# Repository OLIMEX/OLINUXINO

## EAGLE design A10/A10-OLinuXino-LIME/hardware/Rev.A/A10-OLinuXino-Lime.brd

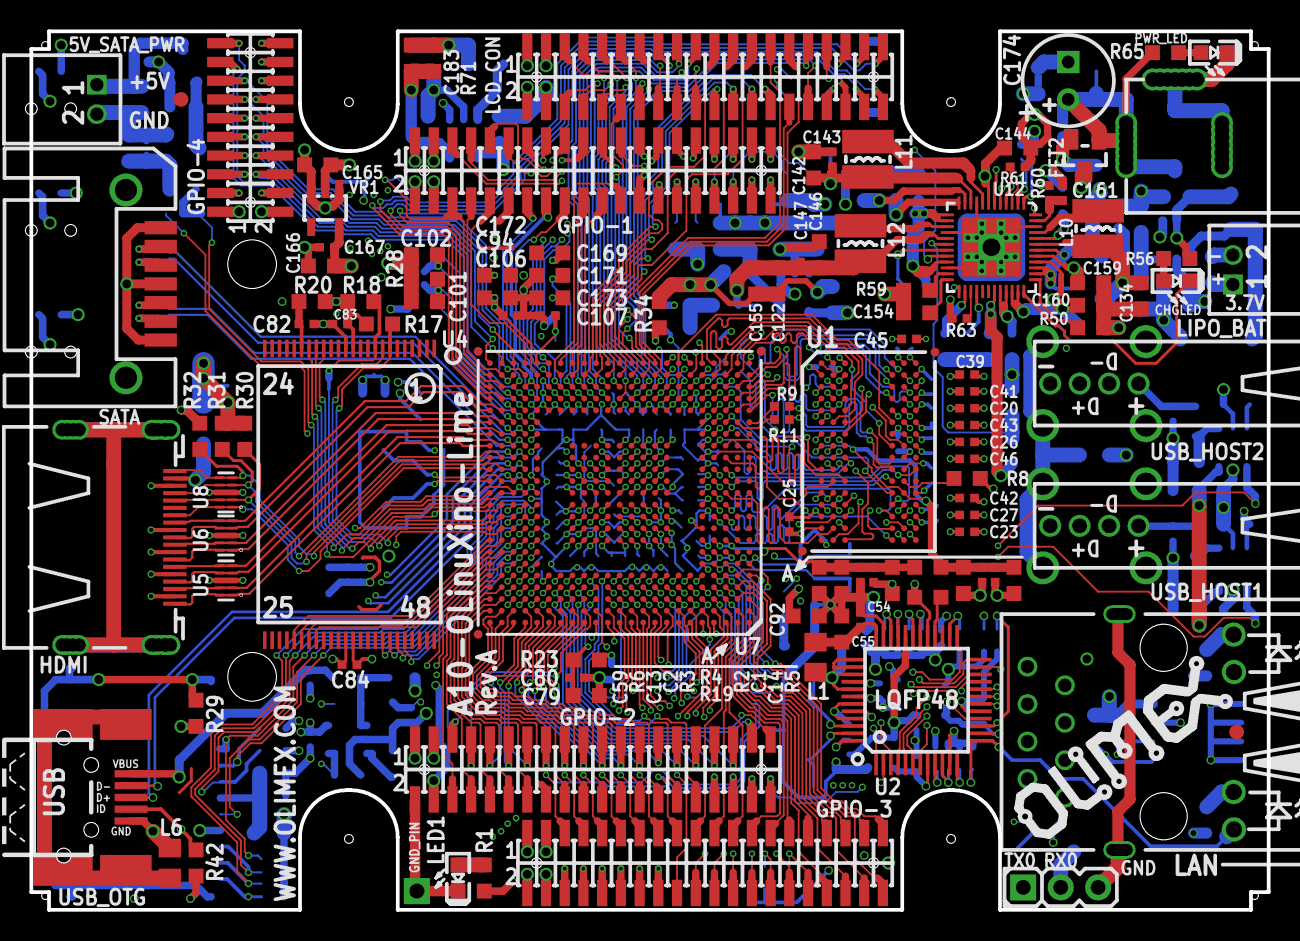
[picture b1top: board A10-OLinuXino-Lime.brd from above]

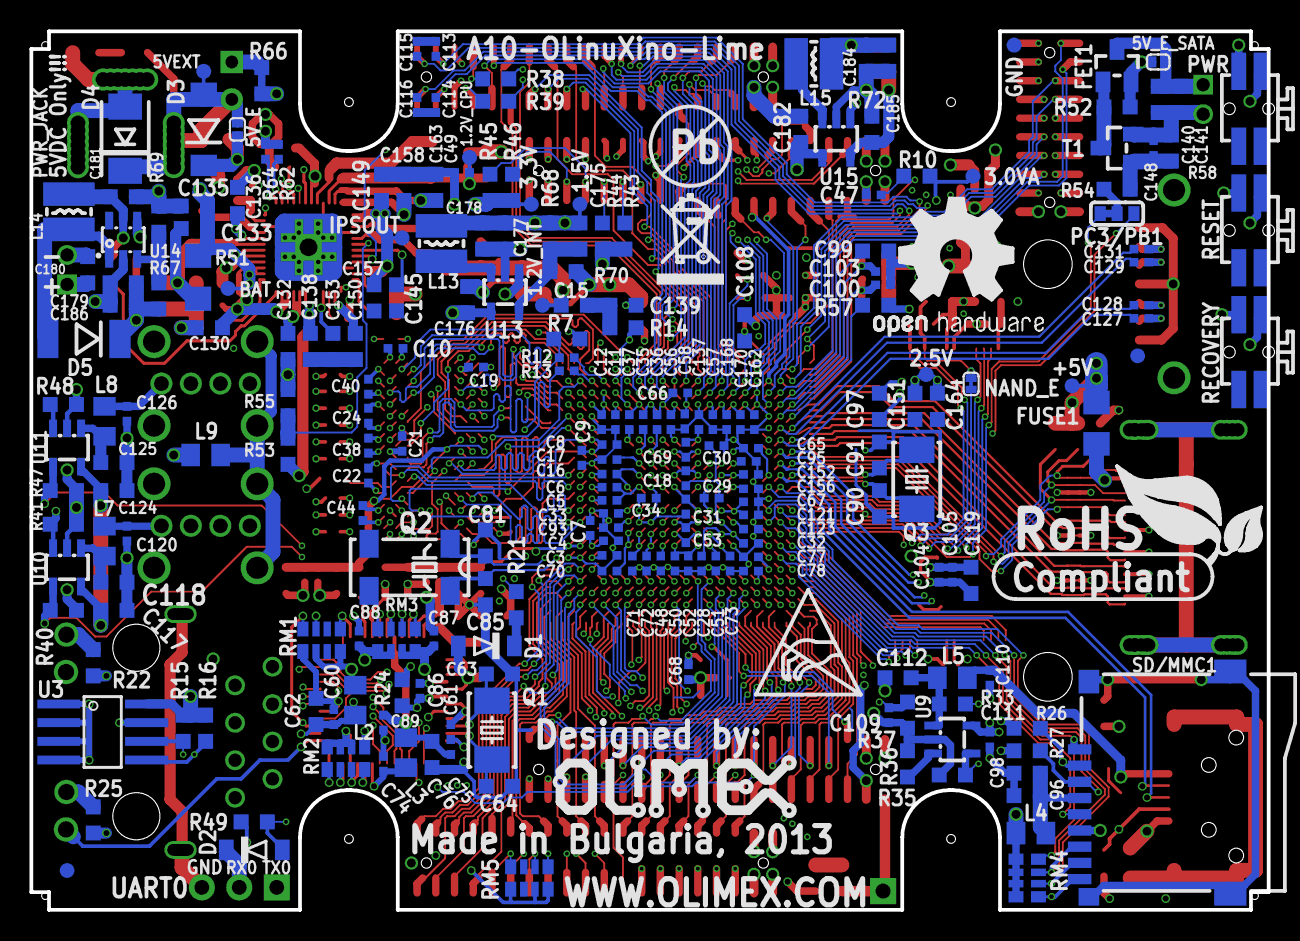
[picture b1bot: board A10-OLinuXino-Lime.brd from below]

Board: 6 copper layers, 84.0 x 59.6 mm, 356 parts (239 on the bottom side), 388 nets.

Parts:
1.2V_CPU, 1.2V_INT, 1.5V, 2.5V, 3.0VA, 3.3V, 5VEXT: TESTPADTESTPAD_40-ROUND; TESTPAD_40-ROUND
5V_E: Open; SJ_1_SMALLER
5V_E_SATA: SJ_1_SMALLER
5V_SATA_PWR: CON2DW02R; DW02R
+5V: TESTPADTESTPAD_40-ROUND; TESTPAD_40-ROUND
BAT: TESTPADTESTPAD_40-ROUND; TESTPAD_40-ROUND
C1, C2, C3, C4, C5, C6, C7, C8, C9, C10, C11, C12, C13, C14, C16, C17, C18, C19, C20, C21, C22, C23, C24, C25, C26, C27, C28, C29, C30, C31, C32, C33, C34, C35, C36, C37, C38, C39, C40, C41, C42, C43, C44, C45, C46, C48, C49, C50, C51, C52, C53, C56, C57, C58, C65, C66, C67, C68, C69, C70, C71, C72, C73, C77, C78, C95, C100, C103, C104, C105, C106, C107, C121, C123, C137, C152, C156, C162, C168, C170: 220nF; C0402_TI
C15, C55, C62, C76, C92, C94, C96, C97, C98, C112, C118, C119, C122, C125, C139, C140, C151, C155, C164, C165, C166, C169, C172, C176, C177, C178, C179, C180, C181, C182, C184, C185, C186: 22uF/6.3V; C0603_DWS
C47, C113, C114, C115, C116, C143, C147, C161: 1nF; C0402_TI
C54, C60, C61, C74, C75, C80, C82, C83, C84, C86, C87, C88, C89, C93, C109, C110, C111, C120, C126, C148, C167: 100nF; C0402_TI
C59: NA; C0603_DWS
C63, C64, C90, C91: 33pF; C0603_DWS
C79, C99, C133, C145, C150, C154: 1uF; C0603_DWS
C81, C85: 10pF; C0603_DWS
C101, C102, C108, C117, C124, C130, C132, C134, C135, C136, C138, C142, C144, C146, C149, C153, C157, C158, C159, C160, C163: 10uF/6.3V; C0603_DWS
C127, C128, C129, C131: 10nF; C0402_TI
C141: NA(22uF/6.3V); C0603_DWS
C171, C173: 470nF; C0603_DWS
C174: 470uF/10V/105C; E2,5-6,3
C175, C183: 22pF; C0603_DWS
CHGLED: LED/YELLOW/0603; LED-0603
D1, D2: 1N5819(S4SOD-123); SOD-123
D3: 1N5822/SS34/SMA; MLL-41
D4: SMBJ6.0A; DO214AA
D5: 1N5822/SS34/SMA; MELF-MLL41
FET1, FET2: IRLML6402; SOT23
FUSE1: FSMD035; 1206
GND: TESTPADTESTPAD_40-ROUND; TESTPAD_40-ROUND
GND_PIN: TESTPAD3; TEST_PAD40/70/SQUARE
GPIO-1, GPIO-2, GPIO-3: ML40YA-V36P-2X20-LF; YA-V36P-2X20-LF
GPIO-4: ML20YA-V36P-2X10-LF; YA-V36P-2X10-LF
HDMI: HDMI-SWM-19
IPSOUT: TESTPADTESTPAD_40-ROUND; TESTPAD_40-ROUND
L1, L2, L3, L5, L6, L7, L8, L9: FB0805/600R/2A; L0805_5MIL_DWS
L4: CL470nH/0805/1.76R/250mA; L0805_5MIL_DWS
L10, L11, L12, L13, L14, L15: 2.2uH/1.5A/DCR<0.1R/CD32; CD32
LAN: RJLBC-060TC1_GND_MILLING; RJLBC-060TC1_MILLING
LCD_CON: ML40YA-V36P-2X20-LF; YA-V36P-2X20-LF
LED1: LED/GREEN/0603; LED-0603
LIPO_BAT: CON2DW02R; DW02R
NAND_E: Close; SJ_1_SMALLER_CLOSE_10MILS
PC3/PB1: SJ_2_SMALL_23_TIED
PWR: SIDE_WTCM-TR(3X4); SW_TAKT3X4
PWR_JACK: YDJ-1136; PWR_JACK_UNI_MILLING
PWR_LED: LED/RED/0603; LED-0603
Q1: 4SB25.000F20E15/5x3.2mm/20ppm/20pF; HCX-4S
Q2: 32768Hz/6pF; MC-306
Q3: 4SB24.000F20E15/5x3.2mm/20ppm/20pF; HCX-4S
R1, R43, R44, R45, R46, R56, R65: 2.2k; R0603_5MIL_DWS
R2, R3, R5, R6, R7, R19, R30, R31: 2k/1%; R0603_5MIL_DWS
R4, R24, R38, R39: NA; R0603_5MIL_DWS
R8: 237R/1%; R0603_5MIL_DWS
R9, R11: 22R; R0402_TI
R10, R26, R53: 100k/1%; R0603_5MIL_DWS
R12, R13: NA(Close_0R); R0402_TI
R14: 330R/1%; R0603_5MIL_DWS
R15, R16: NA(2.2k); R0603_5MIL_DWS
R17, R18, R20, R27, R29, R35, R37, R40, R47, R49, R52, R54: 10k; R0603_5MIL_DWS
R21, R23, R32, R42: 47k; R0603_5MIL_DWS
R22, R25: 560R; R0603_5MIL_DWS
R28, R55, R59: 200k/1%; R0603_5MIL_DWS
R33, R58, R68, R71: 4.99k/1%; R0603_5MIL_DWS
R34: NA(0R); R0603_5MIL_DWS
R36, R41, R48: 13k/1%; R0603_5MIL_DWS
R50: 100R; R0603_5MIL_DWS
R51: 0.03R/1%; R1206_5MIL_WS
R57: 191R/1%; R0603_5MIL_DWS
R60, R61, R62, R63, R64: 2.2k; R0402_TI
R66: 0R(Board_Mounted); 0603_0R
R67: 8.25k/1%; R0603_5MIL_DWS
R69, R72: 1.1k/1%; R0603_5MIL_DWS
R70: 3.32k/1%; R0603_5MIL_DWS
RECOVERY: SIDE_WTCM-TR(3X4); SW_TAKT3X4
RESET: SIDE_WTCM-TR(3X4); SW_TAKT3X4
RM1, RM2: RA1206_(4X0603)_4B8_4.7k; R_MATRIX_4
RM3: RA1206_(4X0603)_4B8_51R; R_MATRIX_4
RM4: RA1206_(4X0603)_4B8_100K; R_MATRIX_4
RM5: RA1206_(4X0603)_4B8_10k; R_MATRIX_4
SATA: SATA-PWA-07
SD/MMC1: MICRO_SD/MMC_CP_NEWTFC-WPAPR-08; TFC-WPAPR-08
T1: BC846B; SOT23
U1: MEM4G16D3EABG-125; FBGA96_MEM
U2: RTL8201CP; LQFP48
U3: AT24C16BN-SH; SO-08MN
U4: H27UBG8T2BTR; TSOP48
U5, U6, U8: NA(RCLAMP0524P); SLP2510P8
U7: A10; TFBGA441
U9, U10, U11: SY6280; SOT23-5
U12: AXP209(QFN48); QFN48
U13, U15: SY8008C(AA)C; SOT23-5
U14: SY7208(SOT23-6); SOT23-6
U16, U17, U18, U19: FIDUCIAL; FIDUCIAL-1X3
U$2: HAMMOND_1593LBK_A10_LIME
U$5: LOGO-OPENHARDWARE_8X8
U$6, U$8: OLIMEX1_V
U$9: PB
U$10: ESD_SYMBOL
U$11: RECYCLE_BIN1/8
U$12: ROHS
UART0: HN1X3
USB_HOST1, USB_HOST2: USB_A_VERTICAL; USB_A_VERTICAL_PTH
USB_OTG: USB-OTG; USB_MINI_9PIN
VR1: AP1231-2.5V(SOT23-5); SOT-23-5

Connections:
5VEXT: 5VEXT.1, 5V_E.1, C132.2, C174.+, D3.A, D4.C, FET2.1, PWR_JACK.+, R65.1, U12.32, U12.33
+5V: 5V_E.2, 5V_E_SATA.1, +5V.1, C111.1, C117.1, C124.1, D3.K, FET1.2, FET2.2, FUSE1.1, GPIO-1.1, GPIO-2.1, GPIO-3.1, LCD_CON.1, R30.2, R31.2, R52.1, U9.5, U10.5, U11.5
+5V_OTG_PWR: C110.1, C138.2, L5.1, R53.1, U12.31, USB_OTG.VBUS
+24V: BAT.1, C133.2, C135.1, C180.2, LIPO_BAT.1, R51.2, U12.38, U12.39, U12.42
BA0: U1.M2, U7.K3
BA1: U1.N8, U7.L4
BA2: U1.M3, U7.K4
CASN: U1.K3, U7.U3
CKE: U1.K9, U7.N3
CLK: R9.1, U1.J7
CLKN: R11.1, U1.K7
CPU-REF: C2.2, C13.2, C59.2, R3.1, R4.2, R6.2, U7.AA8, U7.H3, U7.H4, U7.Y5
DDR3_ODT: R13.1, U1.K1
DDR3_RST: R7.1, R12.1, U1.T2
DDR_VREF: C1.2, C14.2, R2.1, R4.1, R5.2, U1.H1, U1.M8
DQ0: U1.E3, U7.AB4
DQ1: U1.F7, U7.AC7
DQ2: U1.F2, U7.AC4
DQ3: U1.F8, U7.AB8
DQ4: U1.H3, U7.AC8
DQ5: U1.H8, U7.AB5
DQ6: U1.G2, U7.AB7
DQ7: U1.H7, U7.AC3
DQ8: U1.D7, U7.AB2
DQ9: U1.C3, U7.Y1
DQ10: U1.C8, U7.AC2
DQ11: U1.C2, U7.Y2
DQ12: U1.A7, U7.AA1
DQ13: U1.A2, U7.AB3
DQ14: U1.B8, U7.W2
DQ15: U1.A3, U7.AC1
ECOL: U2.1, U7.D13
ECRS: U2.23, U7.E12
EMDC: U2.25, U7.E10
EMDIO: RM1.1.1, U2.26, U7.D11
EPHY-RST#: R24.1, U7.C13
ERXCK: U2.16, U7.D9
ERXD0: U2.21, U7.E6
ERXD1: U2.20, U7.D6
ERXD2: U2.19, U7.E5
ERXD3: U2.18, U7.D5
ERXDV: U2.22, U7.D10
ERXERR: U2.24, U7.E9
ETXCK: U2.7, U7.D12
ETXD0: U2.6, U7.E8
ETXD1: U2.5, U7.D8
ETXD2: U2.4, U7.E7
ETXD3: U2.3, U7.D7
ETXEN: U2.2, U7.E11
EXTEN: U12.20, U14.4, U15.1
FMINL: GPIO-4.19, U7.Y20
FMINR: GPIO-4.17, U7.Y21
GND: 5V_SATA_PWR.2, C3.1, C4.1, C5.1, C6.1, C7.1, C8.1, C9.1, C10.1, C11.1, C12.1, C13.1, C14.1, C15.1, C16.1, C17.1, C18.1, C19.1, C20.1, C21.1, C22.1, C23.1, C24.1, C25.1, C26.1, C27.1, C28.1, C29.1, C30.1, C31.1, C32.1, C33.1, C34.1, C35.1, C36.1, C37.1, C38.1, C39.1, C40.1, C41.1, C42.1, C43.1, C44.1, C45.1, C46.1, C48.1, C49.1, C50.1, C51.1, C52.1, C53.1, C54.1, C55.1, C56.1, C57.1, C58.1, C59.1, C60.1, C61.1, C62.1, C63.1, C64.1, C65.1, C66.1, C67.1, C68.1, C69.1, C70.1, C71.1, C72.1, C73.1, C74.2, C75.2, C76.2, C77.1, C78.1, C79.1, C80.1, C81.1, C82.1, C83.1, C84.1, C85.1, C86.1, C87.1, C88.1, C89.1, C90.1, C91.1, C92.1, C93.1, C94.1, C95.1, C96.1, C98.1, C104.1, C105.1, C106.1, C107.1, C108.1, C109.2, C110.2, C111.2, C112.1, C113.1, C114.1, C115.1, C116.1, C117.2, C118.1, C119.1, C120.2, C121.1, C122.1, C123.1, C124.2, C125.1, C126.2, C130.1, C132.1, C134.2, C135.2, C136.2, C137.2, C138.1, C139.1, C140.1, C141.1, C142.2, C143.2, C144.2, C145.1, C146.2, C147.2, C148.2, C149.2, C150.1, C151.1, C152.1, C153.2, C154.1, C155.1, C156.1, C157.1, C158.2, C159.2, C160.2, C161.1, C162.2, C163.2, C164.1, C165.2, C166.2, C167.2, C168.2, C169.1, C170.2, C171.1, C172.1, C173.1, C174.-, C176.2, C177.2, C178.2, C179.2, C180.1, C181.1, C182.2, C184.2, C185.2, C186.2, D4.A, GND.1, GND_PIN.P$1, GPIO-1.2, GPIO-2.2, GPIO-3.2, GPIO-3.4, GPIO-4.2, HDMI.2, HDMI.5, HDMI.8, HDMI.11, HDMI.17, HDMI.SH1, HDMI.SH2, HDMI.SH3, HDMI.SH4, L6.1, L9.1, LAN.GND1, LAN.GND2, LCD_CON.2, LCD_CON.4, LED1.C, LIPO_BAT.2, PWR.2_1, PWR_JACK.-, PWR_JACK.--, PWR_LED.C, R5.1, R6.1, R8.1, R14.1, R19.1, R25.2, R29.2, R32.2, R34.2, R35.1, R36.1, R37.1, R40.1, R41.1, R47.1, R48.1, R50.1, R55.2, R57.1, R58.1, R59.1, R61.1, R63.2, R66.1, R69.2, R70.2, R72.2, RECOVERY.1_1, RM1.4.2, RM2.2.1, RM2.3.1, RM2.4.1, SATA.1, SATA.4, SATA.7, SD/MMC1.6, T1.2, U1.A9, U1.B1, U1.B3, U1.B9, U1.D1, U1.D8, U1.E1, U1.E2, U1.E8, U1.F9, U1.G1, U1.G8, U1.G9, U1.J2, U1.J8, U1.M1, U1.M9, U1.P1, U1.P9, U1.T1, U1.T9, U2.11, U2.17, U2.29, U2.35, U2.40, U2.43, U2.45, U3.1, U3.2, U3.3, U3.4, U3.7, U4.13, U4.36, U5.3, U5.8, U6.3, U6.8, U7.AA18, U7.G3, U7.G4, U7.H16, U7.J5, U7.J11, U7.K5, U7.K11, U7.K12, U7.K13, U7.K14, U7.L10, U7.L11, U7.L12, U7.L13, U7.L14, U7.M9, U7.M10, U7.M11, U7.M12, U7.M13, U7.M14, U7.N5, U7.N10, U7.N11, U7.N12, U7.N13, U7.N14, U7.P5, U7.P10, U7.P11, U7.P12, U7.P13, U7.P14, U7.P15, U7.R11, U7.R12, U7.R13, U7.T9, U7.T11, U7.T12, U7.U5, U7.V5, U7.V19, U7.W9, U7.W10, U7.W11, U7.W18, U7.Y7, U7.Y8, U7.Y18, U8.3, U8.8, U9.2, U10.2, U11.2, U12.9, U12.16, U12.22, U12.46, U12.N1, U12.N2, U12.N3, U12.N4, U12.N5, U12.N6, U12.N7, U12.N8, U12.N9, U12.N10, U12.N11, U12.N12, U12.N13, U12.N14, U12.N15, U12.N16, U12.N17, U12.VSS, U13.2, U14.2, U15.2, UART0.3, USB_HOST1.4, USB_HOST2.4, USB_OTG.GND, VR1.2
GNDA: C47.2, C97.1, C99.1, C100.1, C101.1, C102.1, C103.1, GPIO-1.4, R28.2, R66.2, U7.U19
GPIO1: R53.2, R55.1, U12.18
GPIO2: GPIO-4.12, U12.5
GPIO3: GPIO-4.14, U12.3
HCEC: HDMI.13, U7.P23, U8.1, U8.10
HDMI_5V_SOURCE: FUSE1.2, HDMI.18
HHPD: HDMI.19, R32.1, U7.P22, U8.5, U8.6
HPCOM: GPIO-1.16, U7.AA19, U7.AA20
HPOUTL: GPIO-1.14, U7.Y19
HPOUTR: GPIO-1.18, U7.W19
HSCL: HDMI.15, R30.1, U7.R23, U8.2, U8.9
HSDA: HDMI.16, R31.1, U7.R22, U8.4, U8.7
HTX0N: HDMI.9, U6.2, U6.9, U7.V22
HTX0P: HDMI.7, U6.1, U6.10, U7.V23
HTX1N: HDMI.6, U5.5, U5.6, U7.U22
HTX1P: HDMI.4, U5.4, U5.7, U7.U23
HTX2N: HDMI.3, U5.2, U5.9, U7.T22
HTX2P: HDMI.1, U5.1, U5.10, U7.T23
HTXCN: HDMI.12, U6.5, U6.6, U7.W22
HTXCP: HDMI.10, U6.4, U6.7, U7.W23
IPSOUT: C130.2, C136.1, C144.1, C149.1, C157.2, C160.1, C176.1, C181.2, C182.1, IPSOUT.1, L14.1, R56.1, RESET.1_1, U12.7, U12.13, U12.14, U12.21, U12.34, U12.35, U12.40, U12.44, U13.4, U14.5, U15.4
LCD_CLK: LCD_CON.31, U7.Y9
LCD_D0: LCD_CON.21, U7.AB15
LCD_D1: LCD_CON.22, U7.AC15
LCD_D2: LCD_CON.23, U7.AB14
LCD_D3: LCD_CON.24, U7.AC14
LCD_D4: LCD_CON.25, U7.AB13
LCD_D5: LCD_CON.26, U7.AC13
LCD_D6: LCD_CON.27, U7.AB12
LCD_D7: LCD_CON.28, U7.AC12
LCD_D8: LCD_CON.13, U7.AB11
LCD_D9: LCD_CON.14, U7.AC11
LCD_D10: LCD_CON.15, U7.Y15
LCD_D11: LCD_CON.16, U7.AA15
LCD_D12: LCD_CON.17, U7.Y14
LCD_D13: LCD_CON.18, U7.AA14
LCD_D14: LCD_CON.19, U7.Y13
LCD_D15: LCD_CON.20, U7.AA13
LCD_D16: LCD_CON.5, U7.Y12
LCD_D17: LCD_CON.6, U7.AA12
LCD_D18: LCD_CON.7, U7.Y11
LCD_D19: LCD_CON.8, U7.AA11
LCD_D20: LCD_CON.9, U7.Y10
LCD_D21: LCD_CON.10, U7.AA10
LCD_D22: LCD_CON.11, U7.AB10
LCD_D23: LCD_CON.12, U7.AC10
LCD_DE: LCD_CON.32, U7.AA9
LCD_HSYNC: LCD_CON.29, U7.AB9
LCD_PWR: LCD_CON.35, U7.C4
LCD_VSYNC: LCD_CON.30, U7.AC9
LDO3_2.8V: C77.2, C159.1, GPIO-2.4, U7.F19, U12.41
LDO4_2.8V: C78.2, C163.1, U7.E18, U12.11
LINEINL: GPIO-4.15, U7.AB20
LINEINR: GPIO-4.13, U7.AB21
LRADC0: C47.1, GPIO-1.6, R10.2, U7.AB23
LRADC1: GPIO-1.8, U7.AB22
MIC1OUTN: GPIO-4.8, U7.AC23
MIC1OUTP: GPIO-4.6, U7.AC22
MICIN1: GPIO-1.10, U7.AC20
MICIN2: GPIO-4.10, U7.AC21
unnamed: C107.2, C108.2, U7.AC19
unnamed: R14.2, U7.AA7
unnamed: R8.2, U1.L8
unnamed: CHGLED.A, R56.2
unnamed: PC3/PB1.2, R54.2
unnamed: R19.2, U2.28
unnamed: D2.C, UART0.2
unnamed: L13.1, U13.3
unnamed: C145.2, U12.19
unnamed: D1.C, R21.2
unnamed: CHGLED.C, U12.36
unnamed: R63.1, U12.27
unnamed: RM1.4.1, U2.15
unnamed: C81.2, Q2.1, U7.F1
unnamed: C148.1, R54.1, R58.2, T1.1
unnamed: FET1.1, R52.2, T1.3
unnamed: C175.2, R68.2, R70.1, U13.5
unnamed: C54.2, C55.2, L1.1, U2.36
unnamed: C179.1, C186.1, D5.1, FET2.3, R67.2
unnamed: 5V_E_SATA.2, 5V_SATA_PWR.1, C140.2, C141.2, FET1.3
unnamed: C86.2, R24.2, RM1.3.1, U2.42
unnamed: C88.2, RM3.1.1, RM3.2.1
unnamed: PWR.1_1, R60.1
unnamed: LAN.1, RM3.4.2, U2.34
unnamed: LAN.2, RM3.3.2, U2.33
unnamed: LAN.7, RM3.2.2, U2.31
unnamed: C171.2, U7.AA16
unnamed: LAN.8, RM3.1.2, U2.30
unnamed: C87.2, RM3.3.1, RM3.4.1
unnamed: RM2.2.2, U2.10
unnamed: RM2.3.2, U2.12
unnamed: LAN.KG, R22.1
unnamed: LAN.AY, RM2.4.2, U2.13
unnamed: C74.1, L3.1, U2.8
unnamed: C75.1, C76.1, C89.2, L3.2, LAN.3, U2.32
unnamed: LAN.KY, R25.1
unnamed: R29.1, SD/MMC1.10, SD/MMC1.11, SD/MMC1.12, SD/MMC1.13
unnamed: L15.1, U15.3
unnamed: C183.2, R71.2, R72.1, U15.5
unnamed: C60.2, C61.2, C62.2, L2.1, U2.14, U2.48
unnamed: R22.2, RM2.1.2, U2.9
unnamed: R36.2, U9.3
unnamed: C112.2, L5.2, R33.2, U9.1
unnamed: R41.2, U10.3
unnamed: C127.2, SATA.2
unnamed: C120.1, L7.2, USB_HOST1.1
unnamed: C128.2, SATA.3
unnamed: C129.2, SATA.5
unnamed: C131.2, SATA.6
unnamed: C85.2, Q2.4, U7.F2
unnamed: R57.2, U7.V21
unnamed: R59.2, U12.23
unnamed: C102.2, C103.2, U7.W21
unnamed: D5.2, L14.2, U14.1
unnamed: C82.2, R20.2, U4.19
unnamed: R50.2, U12.37
unnamed: R67.1, R69.1, U14.3
unnamed: L10.1, U12.45
unnamed: C133.1, C134.1, L10.2, R51.1, U12.43
unnamed: PWR_LED.A, R65.2
unnamed: L11.1, U12.8
unnamed: L12.1, U12.15
unnamed: C154.2, U12.24
unnamed: C99.2, U7.W20
unnamed: R48.2, U11.3
unnamed: C161.2, R60.2, U12.47
unnamed: R61.2, RESET.2_1, U12.4
unnamed: C100.2, C101.2, R28.1, U7.V20
unnamed: R34.1, U7.T10
unnamed: C118.2, L7.1, U10.1
unnamed: L9.2, USB_HOST1.P$3, USB_HOST1.P$4, USB_HOST2.P$3, USB_HOST2.P$4
unnamed: C126.1, L8.2, USB_HOST2.1
unnamed: C125.2, L8.1, U11.1
unnamed: C173.2, U7.Y16
unnamed: LCD_CON.33, R38.1
unnamed: LCD_CON.34, R39.1
unnamed: LED1.A, R1.2
unnamed: NAND_E.1, R18.2, U4.9
unnamed: L6.2, USB_OTG.GND1, USB_OTG.GND2, USB_OTG.GND3, USB_OTG.GND4
NALE: U4.17, U7.M22
NCE0: NAND_E.2, U7.K23
NCLE: U4.16, U7.L23
NDQ0: U4.29, U7.H23
NDQ1: U4.30, U7.H22
NDQ2: U4.31, U7.G23
NDQ3: U4.32, U7.G22
NDQ4: U4.41, U7.H21
NDQ5: U4.42, U7.H20
NDQ6: U4.43, U7.G21
NDQ7: U4.44, U7.G20
NMI_N: GPIO-4.4, R21.1, U7.F5, U12.48
NRB0: R17.2, U4.7, U7.J23
NRE: U4.8, U7.K22
NWE: U4.18, U7.M23
ODT0: R13.2, U7.AA5
PB2/PWM0: LCD_CON.36, U7.A14
PB3: GPIO-3.6, R38.2, U7.B14
PB4: GPIO-3.8, R39.2, U7.A13
PB5: GPIO-3.10, U7.B13
PB6: GPIO-3.12, U7.A12
PB7: GPIO-3.14, U7.B12
PB8/SATA-PWR-EN: GPIO-3.16, PC3/PB1.1, U7.A11
PB10: GPIO-3.18, U7.C11
PB11: GPIO-3.20, U7.C10
PB12: GPIO-3.22, U7.C9
PB13: GPIO-3.24, U7.B11
PB14: GPIO-3.26, RM5.1.1, U7.A10
PB15: GPIO-3.28, RM5.2.1, U7.B10
PB16: GPIO-3.30, U7.A9
PB17: GPIO-3.32, RM5.4.1, U7.B9
PB18: GPIO-1.36, R15.2, R46.1, U3.6, U7.A8
PB19: GPIO-1.34, R16.1, R45.1, U3.5, U7.B8
PB20: GPIO-1.32, R44.1, U7.C8
PB21: GPIO-1.30, R43.1, U7.C7
PC3/SATA-PWR-EN: GPIO-1.29, PC3/PB1.3, U7.L22
PC7: GPIO-4.16, U7.J22
PC16: GPIO-4.18, U7.M21
PC17: GPIO-4.20, U7.F23
PC18: GPIO-1.31, U7.F22
PC19: GPIO-1.33, U7.L21
PC20: GPIO-1.35, U7.K21
PC21: GPIO-1.37, U7.J21
PC22: GPIO-1.39, U7.J20
PC23: GPIO-1.40, U7.G19
PC24: GPIO-1.38, U7.F21
PE0: GPIO-2.6, U7.E23
PE1: GPIO-2.8, U7.E22
PE2: GPIO-2.10, U7.D23
PE3: GPIO-2.12, U7.D22
PE4: GPIO-2.14, U7.C23
PE5: GPIO-2.16, U7.C22
PE6: GPIO-2.18, U7.B23
PE7: GPIO-2.20, U7.B22
PE8: GPIO-2.22, U7.A23
PE9: GPIO-2.24, U7.A22
PE10: GPIO-2.26, U7.B21
PE11: GPIO-2.28, U7.A21
PG0: GPIO-1.5, U7.F20
PG1: GPIO-1.7, U7.E21
PG2: GPIO-1.9, U7.E20
PG3: GPIO-1.11, U7.D21
PG4: GPIO-1.13, U7.D20
PG5: GPIO-1.15, U7.C21
PG6: GPIO-1.17, U7.E19
PG7: GPIO-1.19, U7.C20
PG8: GPIO-1.21, U7.D19
PG9: GPIO-1.23, U7.C19
PG10: GPIO-1.25, U7.D18
PG11: GPIO-1.27, U7.C18
PH0: GPIO-3.7, U7.A6
PH2/LED: R1.1, U7.C6
PH7: GPIO-3.9, U7.B4
PH9: GPIO-3.11, U7.D4
PH10: GPIO-3.13, U7.A3
PH11: GPIO-3.15, U7.B3
PH12: GPIO-3.17, U7.C3
PH13: GPIO-3.19, U7.A2
PH14: GPIO-3.21, U7.B2
PH15: GPIO-3.23, U7.A1
PH16: GPIO-3.25, U7.B1
PH17: GPIO-3.27, U7.C1
PH18: GPIO-3.29, U7.C2
PH19: GPIO-3.31, U7.D1
PH20: GPIO-3.33, U7.D2
PH21: GPIO-3.35, U7.D3
PH22: GPIO-3.37, U7.E1
PH23: GPIO-3.39, U7.E2
PH24: GPIO-3.34, U7.E3
PH25: GPIO-3.36, U7.E4
PH26: GPIO-3.38, U7.F3
PH27: GPIO-3.40, U7.F4
PI0: GPIO-2.9, U7.A20
PI1: GPIO-2.11, U7.B20
PI2: GPIO-2.13, U7.A19
PI3: GPIO-2.15, U7.B19
PI4: GPIO-2.17, U7.A18
PI5: GPIO-2.19, U7.B18
PI6: GPIO-2.21, U7.A17
PI7: GPIO-2.23, U7.B17
PI8: GPIO-2.25, U7.A16
PI9: GPIO-2.27, U7.B16
PI10: GPIO-2.29, U7.C17
PI11: GPIO-2.31, U7.D17
PI12: GPIO-2.33, U7.C16
PI13: GPIO-2.35, U7.D16
PI14: GPIO-2.37, U7.C15
PI15: GPIO-2.39, U7.D15
PI16: GPIO-2.40, U7.E17
PI17: GPIO-2.38, U7.E16
PI18: GPIO-2.36, U7.E15
PI19: GPIO-2.34, U7.D14
PI20: GPIO-2.32, U7.E14
PI21: GPIO-2.30, U7.E13
RASN: U1.J3, U7.T4
RESET_N: C79.2, C80.2, GPIO-3.5, R23.1, U7.C14, U12.25
SA0: U1.N3, U7.W4
SA1: U1.P7, U7.R4
SA2: U1.P3, U7.U4
SA3: U1.N2, U7.M4
SA4: U1.P8, U7.Y4
SA5: U1.P2, U7.N4
SA6: U1.R8, U7.V4
SA7: U1.R2, U7.M3
SA8: U1.T8, U7.AA3
SA9: U1.R3, U7.P4
SA10: U1.L7, U7.L3
SA11: U1.R7, U7.W3
SA12: U1.N7, U7.P3
SA13: U1.T3, U7.Y3
SA14: U1.T7, U7.R3
SA15: U1.M7, U7.AA4
SATA-RXM: C129.1, U7.U20
SATA-RXP: C131.1, U7.U21
SATA-TXM: C128.1, U7.T21
SATA-TXP: C127.1, U7.T20
SCK: R9.2, U7.V1
SCK#: R11.2, U7.V2
SCS0: U1.L2, U7.V3
SD0-CLK: SD/MMC1.5, U7.L20
SD0-CMD: R27.1, SD/MMC1.3, U7.L19
SD0-D0: RM4.2.2, SD/MMC1.7, U7.M19
SD0-D1: RM4.3.2, SD/MMC1.8, U7.M20
SD0-D2: RM4.1.2, SD/MMC1.1, U7.K19
SD0-D3: R26.1, SD/MMC1.2, U7.K20
SD0-DET#: RM4.4.2, SD/MMC1.9, U7.B6
SDQM0: U1.E7, U7.AC6
SDQM1: U1.D3, U7.W1
SDQS0: U1.F3, U7.AB6
SDQS0_N: U1.G3, U7.AC5
SDQS1: U1.C7, U7.AB1
SDQS1_N: U1.B7, U7.AA2
SD_VCC: C96.2, C98.2, L4.2, SD/MMC1.4
SRST: R12.2, U7.AA6
TPX1: C113.2, LCD_CON.37, U7.Y22
TPX2: C114.2, LCD_CON.38, U7.AA22
TPY1: C115.2, LCD_CON.39, U7.Y23
TPY2: C116.2, LCD_CON.40, U7.AA23
TVIN0: GPIO-4.5, U7.AC18
TVIN1: GPIO-4.7, U7.AB18
TVIN2: GPIO-4.9, U7.AA17
TVIN3: GPIO-4.11, U7.Y17
TVOUT3: GPIO-4.3, U7.AB17
TWI0-SCK: GPIO-2.5, R62.1, U7.A15, U12.2
TWI0-SDA: GPIO-2.7, R64.1, U7.B15, U12.1
UART0-RX: D2.A, GPIO-1.26, R49.1, U7.B7
UART0-TX: GPIO-1.28, U7.A7, UART0.1
UBOOT_SEL: RECOVERY.2_1, U7.W8
UDM0: U7.N20, USB_OTG.D-
UDM1: U7.P20, USB_HOST1.2
UDM2: U7.R20, USB_HOST2.2
UDP0: U7.N21, USB_OTG.D+
UDP1: U7.P21, USB_HOST1.3
UDP2: U7.R21, USB_HOST2.3
USB0-DRV: R35.2, U7.C12, U9.4, U12.6
USB0-IDDET: R42.2, U7.B5, USB_OTG.ID
USB0-VBUSDET: C109.1, R33.1, R37.2, U7.C5
USB1-DRV: R40.2, U7.A4, U10.4
USB2-DRV: R47.2, U7.A5, U11.4
V+: 1.5V.1, C1.1, C2.1, C3.2, C4.2, C5.2, C6.2, C7.2, C8.2, C9.2, C10.2, C11.2, C12.2, C19.2, C20.2, C21.2, C22.2, C23.2, C24.2, C25.2, C26.2, C27.2, C38.2, C39.2, C40.2, C41.2, C42.2, C43.2, C44.2, C45.2, C46.2, C175.1, C177.1, C178.1, L13.2, R2.2, R3.2, R7.2, R68.1, U1.A1, U1.A8, U1.B2, U1.C1, U1.C9, U1.D2, U1.D9, U1.E9, U1.F1, U1.G7, U1.H2, U1.H9, U1.K2, U1.K8, U1.N1, U1.N9, U1.R1, U1.R9, U7.G5, U7.H5, U7.L5, U7.M5, U7.R5, U7.T5, U7.W5, U7.W6, U7.W7, U7.Y6
VCC: 3.3V.1, C56.2, C57.2, C58.2, C65.2, C66.2, C67.2, C68.2, C69.2, C70.2, C71.2, C72.2, C73.2, C83.2, C84.2, C94.2, C95.2, C104.2, C105.2, C106.2, C119.2, C121.2, C137.1, C139.2, C165.1, C168.1, C169.2, C170.1, C172.2, C183.1, C184.1, C185.1, D1.A, GPIO-1.3, GPIO-2.3, GPIO-3.3, GPIO-4.1, L1.2, L2.2, L4.1, L15.2, LAN.AG, LCD_CON.3, R15.1, R16.2, R17.1, R18.1, R20.1, R23.2, R26.2, R27.2, R42.1, R43.2, R44.2, R45.2, R46.2, R49.2, R62.2, R64.2, R71.1, RM1.1.2, RM1.3.2, RM2.1.1, RM4.1.1, RM4.2.1, RM4.3.1, RM4.4.1, RM5.1.2, RM5.2.2, RM5.4.2, U2.37, U2.38, U2.39, U2.41, U2.44, U3.8, U4.12, U4.37, U7.AB19, U7.H8, U7.H9, U7.H10, U7.H15, U7.H19, U7.J8, U7.J9, U7.J10, U7.J14, U7.J19, U7.L15, U7.L16, U7.N19, U7.P16, U7.T13, U7.W12, U7.W13, U7.W14, U7.W15, U7.W16, VR1.1, VR1.3
VCC/2: 1.2V_CPU.1, C48.2, C49.2, C50.2, C51.2, C52.2, C53.2, C142.1, C143.1, L11.2, U7.H11, U7.H12, U7.H13, U7.H14, U7.J12, U7.J13, U12.10
VCCINT: 1.2V_INT.1, C15.2, C16.2, C17.2, C18.2, C28.2, C29.2, C30.2, C31.2, C32.2, C33.2, C34.2, C35.2, C36.2, C37.2, C122.2, C123.2, C146.1, C147.1, C155.2, C156.2, L12.2, U7.J15, U7.J16, U7.K9, U7.K10, U7.K15, U7.K16, U7.L8, U7.L9, U7.M8, U7.M15, U7.M16, U7.N9, U7.P9, U7.R9, U7.R10, U7.T8, U12.17
VDD: 2.5V.1, C151.2, C152.2, C162.1, C164.2, C166.1, C167.1, U7.N15, U7.N16, U7.W17, VR1.5
VDD_RTC: C92.2, C93.2, C153.1, U7.K8, U12.28
VGA-B: GPIO-1.22, U7.AB16
VGA-G: GPIO-1.20, U7.AC16
VGA-R: GPIO-1.24, U7.AC17
VINT: C150.2, U12.26
VMIC: GPIO-1.12, U7.AA21
VPP: 3.0VA.1, C97.2, C158.1, R10.1, U7.T19, U12.12, U13.1
WEN: U1.L3, U7.T3
XTALI: C90.2, Q3.2, U7.N23
XTALI1: C63.2, Q1.2, U2.46
XTALO: C91.2, Q3.1, U7.N22
XTALO1: C64.2, Q1.1, U2.47
